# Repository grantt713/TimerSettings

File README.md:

# TimerSettings
arduino code for timer settings device

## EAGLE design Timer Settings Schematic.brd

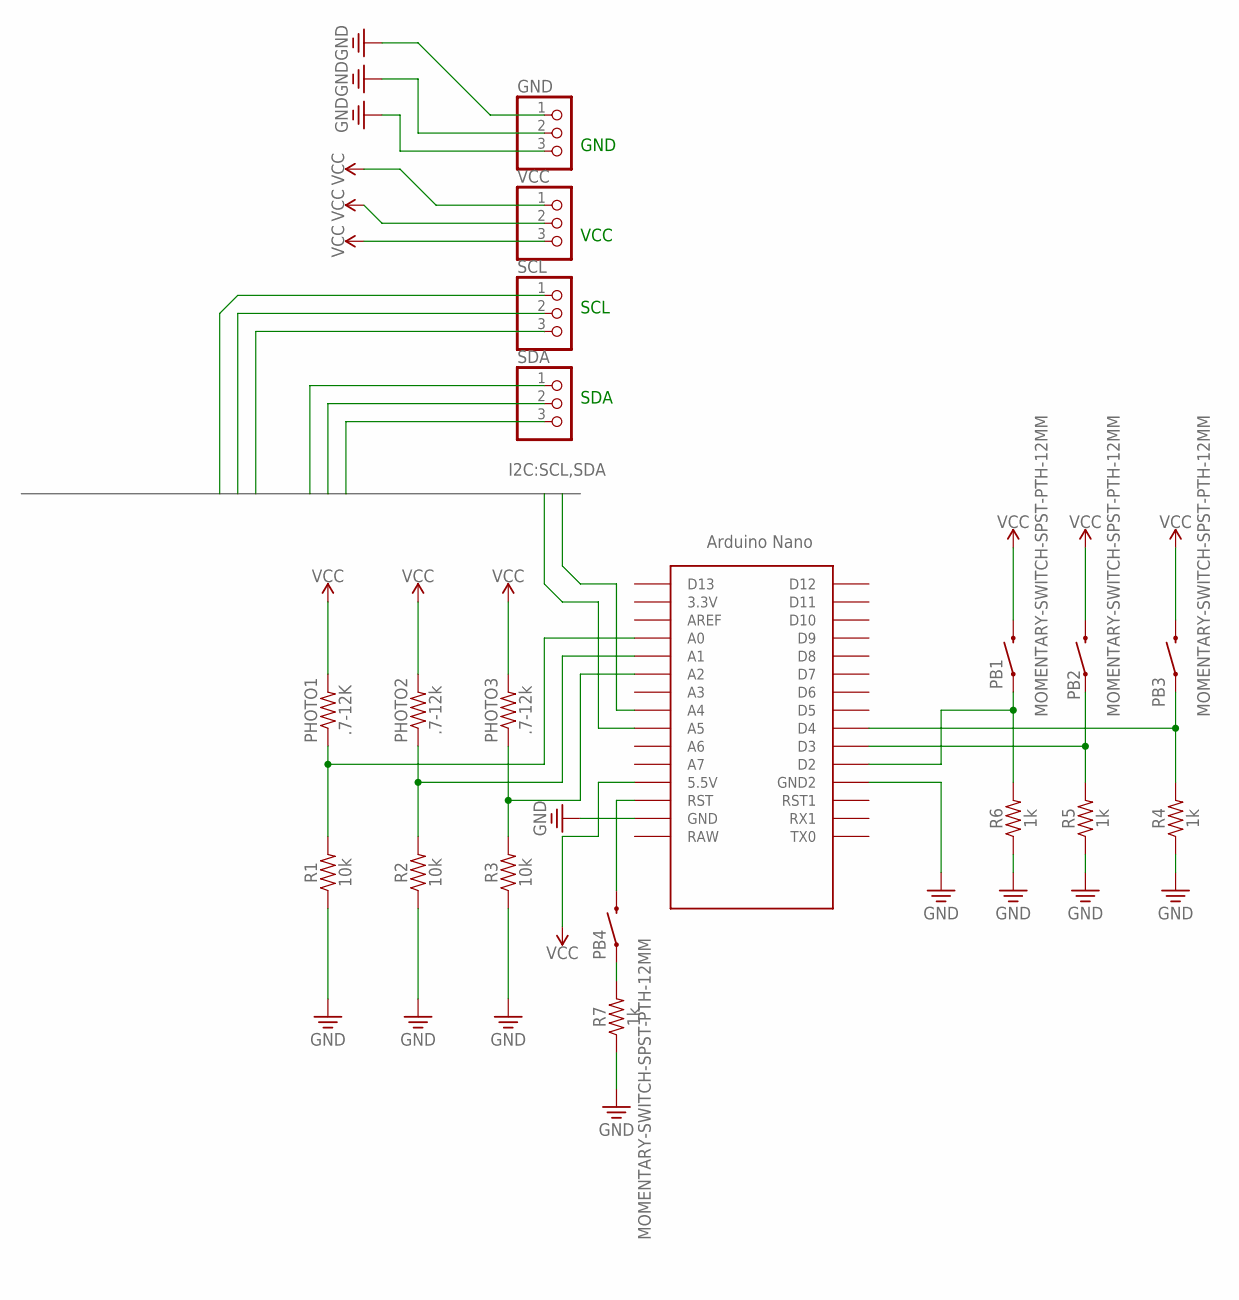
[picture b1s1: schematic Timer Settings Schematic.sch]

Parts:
GND: PINHD-1X3CB; 1X03-CLEANBIG
PB1, PB2, PB3, PB4: MOMENTARY-SWITCH-SPST-PTH-12MM; TACTILE_SWITCH_PTH_12MM
PHOTO1: .7-12K; AXIAL-0.3
PHOTO2, PHOTO3: .7-12k; AXIAL-0.3
R1, R2, R3: 10k; AXIAL-0.3
R4, R5, R6, R7: 1k; AXIAL-0.3
SCL: PINHD-1X3CB; 1X03-CLEANBIG
SDA: PINHD-1X3CB; 1X03-CLEANBIG
U$1: NANO
VCC: PINHD-1X3CB; 1X03-CLEANBIG

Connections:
GND: GND.1, GND.2, GND.3, R1.P$1 (1), R2.P$1 (1), R3.P$1 (1), R4.P$1 (1), R5.P$1 (1), R6.P$1 (1), R7.P$1 (1), U$1.GND, U$1.GND1 (GND2)
unnamed: PB1.1, R6.P$2 (2), U$1.D2
unnamed: PB2.1, R5.P$2 (2), U$1.D3
unnamed: PB3.1, R4.P$2 (2), U$1.D4
unnamed: PHOTO3.P$1 (1), R3.P$2 (2), U$1.A2
unnamed: PHOTO2.P$1 (1), R2.P$2 (2), U$1.A1
unnamed: PHOTO1.P$1 (1), R1.P$2 (2), U$1.A0
unnamed: PB4.1, R7.P$2 (2)
unnamed: PB4.3 (2), U$1.RST
SCL: SCL.1, SCL.2, SCL.3, U$1.A5
SDA: SDA.1, SDA.2, SDA.3, U$1.A4
VCC: PB1.3 (2), PB2.3 (2), PB3.3 (2), PHOTO1.P$2 (2), PHOTO2.P$2 (2), PHOTO3.P$2 (2), U$1.5V (5.5V), VCC.1, VCC.2, VCC.3

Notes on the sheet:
SDA
SCL
VCC
GND

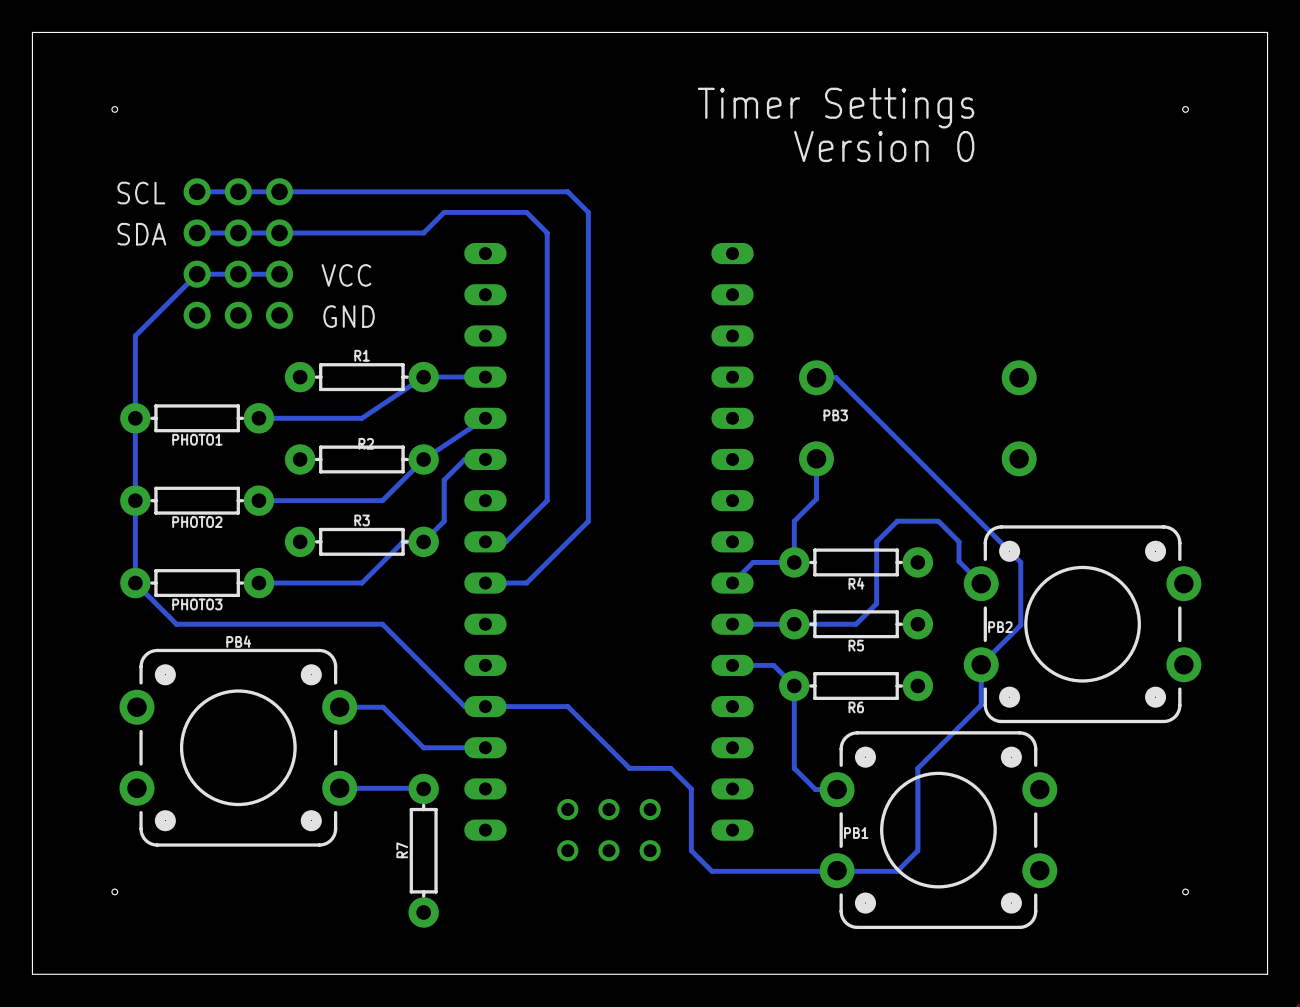
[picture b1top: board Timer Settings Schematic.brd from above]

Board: 2 copper layers, 76.2 x 58.1 mm, 19 parts (1 on the bottom side), 12 nets.

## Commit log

2020-06-23 Add files via upload
    updates
2020-06-24 Add files via upload
    Many of the files are isolated tests. 3StageMultLights should be the master code.
2020-06-24 Add files via upload
    added up to the third LCD display.. has not been tested yet
2020-06-25 Add files via upload
    final product
2020-11-25 Rename 4StageMultLights.ino to FinalTimerCode.ino
    This is the final code for the timer box.
2020-11-25 Eagle Schematics
    Circuitry and PCB Schematic and JPEGs
2020-12-09 Add files via upload
    STL files to be printed
2020-12-17 Add files via upload
    THIS IS THE FINAL CODE AS OF 12/17/20
2020-12-18 Delete 2LCD_Displays.ino
    delete version
2020-12-18 Delete 3StageLightDetect.ino
    delete version
2020-12-18 Delete ButtonTest.ino
    delete button test
2020-12-18 Delete PB_RedOrGreen.ino
    delete
2020-12-18 Delete Final_Version_for_testing_single_light.ino
    delete
2020-12-18 Delete DoneTest.ino
    delete
2020-12-18 Delete FinalTimerCode.ino
    delete
2020-12-18 Delete DetectLight.ino
    delete
2020-12-18 Delete 3StageMultLights.ino
    delete
2020-12-18 Delete learnMillis.ino
    delete
2020-12-18 Update and rename README.md to READ_THIS_HOW_TO_USE_&_NOTES.md
    instructions

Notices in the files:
parts and their libraries:
SparkFun-Switches: Licensing: Creative Commons ShareAlike 4.0 International - https://creativecommons.org/licenses/by-sa/4.0
